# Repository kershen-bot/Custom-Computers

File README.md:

# Custom-Computer

 This is a fully custom laptop that is built around a LattePanda Mu, which is a computer module that is credit card-sized. This project took around two to three and a half months. This project is inspired by Ben Makes Everything and Bryan. The specific video by Ben Makes Everything that I used is "https://www.youtube.com/watch?v=o00P7wHbd2c," and the video by Bryan that I used is "https://www.youtube.com/watch?v=fks3PBodyiE." Bryan's website is "https://www.byran.ee/" 

 Below is an image of the full shell of the custom laptop without the hinge mechanism and the internal components.

------------------------------------------------------------------------------------------------------------------------------------------

Configuration of the Lattepanda Mu,
------------------------------------------------------------------------------------------------------------------------------------------
  The exact size of the Lattepanda Mu is 69.6MM by 60MM, and the standard credit card is 85.6MM by 54MM it is very. The Lattepanda Mu has an  Intel X86 chip. It can be configured with an   N100  or an  N305 chip.  The ram that on the Lattepanda Mu is 16GB of LPDDR5 4800MT/s, and for storage, it can be equipped with an M.2 2230 NVME SSD or slash and a 64GB eMMC 5.1 Storage. And of course it has a wifi card, so you can have wifi. 

Configuration of the LattePanda Mu,
The configuration of the full device is shown below as an image.
------------------------------------------------------------------------------------------------------------------------------------------

The Keyboard,
------------------------------------------------------------------------------------------------------------------------------------------
  The keyboard is a split Ortholinear keyboard because Ortholinear keyboards are easier and more natural to use. The keyboard is a fork of  Ben Makes Everything's first keyboard from his video "Building a LattePanda Mu Cyberdeck." The link to his video is https://www.youtube.com/watch?v=o00P7wHbd2c, and the time that the Ortholinear keyboard is mentioned is between the times 5:10 and 8:45. I learned how to make a  keyboard from "https://www.youtube.com/@joe_scotto"

The Trackpad on the computer,
------------------------------------------------------------------------------------------------------------------------------------------
 The trackpad is made by the company Azoteq, and the exact trackpad that I use is the PXM0091. Azoteq says itself "The IQS9150 is a generic and configurable trackpad device aimed to be suitable for numerous design variations and requirements. The PXM0091 utilizes the IQS9150 to provide high-performance multitouch (linearity, accuracy, low-noise) trackpad outputs, switch input, and an on-chip gesture recognition engine. The website that I got it from was "https://seltech-intl.com/datasheets/pxm0091.pdf." 

The ports on the Laptop,
------------------------------------------------------------------------------------------------------------------------------------------
  The laptop has four USB ports in the style of a Raspberry Pi. The HDMI port is on the back, like some gaming laptops, such as the HP OMEN MAX 16. There are a few internal USB ports, but not use the traditional ribbon connectors and cables; instead, it is using a JST connector, and there is an internal amp on the mainboard, but the BIOS and  LattePanda Mu software do not support I2S.  LattePanda said, "They will support I2S in the near future." So I decided to use a USB to audio using a rapberry pi pico to I2S, then I2S to a  USB audio converter, then to the speaker. 

The Power System
------------------------------------------------------------------------------------------------------------------------------------------
  The power button is on the main board, and it is internal, but the reason why is that when testing it, you don't need to go to the side of the laptop. But how to turn on the computer, you may ask. There is a keyboard switch on the side of the computer that is wired to the internal power button. All so there is a switch that connects directly to the battery and skips the main board and all of the software, so in an emergency, you canan switch it, and all power is shut off immediately  The battery is a 18650 4S5P battery pacl connected to an trusted AliExpress BMS, which is the  "140W 2S 3S 4S 5S 6S Lithium Battery Charging Board Bidirectional Fast Charging Li-ion Lifepo4 BMS Charger Type-C IP2366 PD3.1". Which is then connected to a 100A ANL fuse. Then it goes to a screw terminal and connects to the main board with another screw terminal, which takes the 9-12 volts from the battery. 

Battery Life of the laptop
------------------------------------------------------------------------------------------------------------------------------------------
  Battery life is a key thing when using a laptop. When you have a small battery, you have a little time on the battery, and when you have a big battery, your batter last a long time.
Number for Battery Life of the laptop
1. The battery life is about 7 hours in high-performance mode.
2. 10 hours on balanced mode.
3. On battery saver mode. It lasts about 15 hours.
  These numbers are done by math but not tested in the real world. The amount of watt-hours in the battery is 120-176 watt-hours. The legal limit for laptops that can go on planes is 99.99 watt-hours, and for battery banks it is 120-176. So if you decide to make this laptop, you can't bring it on a plane, so you have to send it to the location.

Sources & bibliography
------------------------------------------------------------------------------------------------------------------------------------------
Here are some sources I used during this project.
Keybourd
1. https://lowprokb.ca/products/kailh-choc-low-profile-switches
2. https://www.youtube.com/watch?v=bBon6WwkdJE
3. https://www.youtube.com/watch?v=8WXpGTIbxlQ
4. https://www.youtube.com/@joe_scotto
5. https://github.com/qmk/qmk_firmware
6. https://qmk.fm/
Trackpad
1. https://www.mouser.com/datasheet/2/42/Azoteq_PXM0057_20220503-2943524.pdf
2. https://www.azoteq.com/product/pxm0091/
3. https://www.mouser.ca/ProductDetail/Azoteq/IQS9150EV02-S?qs=wT7LY0lnAe1UXNco1GldIA%3D%3D
4. https://www.mouser.ca/datasheet/3/931/1/iqs9150ev02_user_guide.pdf
Battery
1. https://www.lipolbattery.com/lithium%20polymer%20battery.html
2. https://www.amazon.ca/s?k=thin+li+po+battery&rh=n%3A667823011%2Cp_n_feature_five_browse-bin%3A23876309011&dc&ds=v1%3A1%2FyLAj4am5oxl1W0bAFB4SyuocLMjKd7XB4K8g09IpI&crid=1DQOK09KIS3O2&qid=1745368113&rnid=23876298011&sprefix=thin+li+po+battery+%2Caps%2C190&ref=sr_nr_p_n_feature_five_browse-bin_1

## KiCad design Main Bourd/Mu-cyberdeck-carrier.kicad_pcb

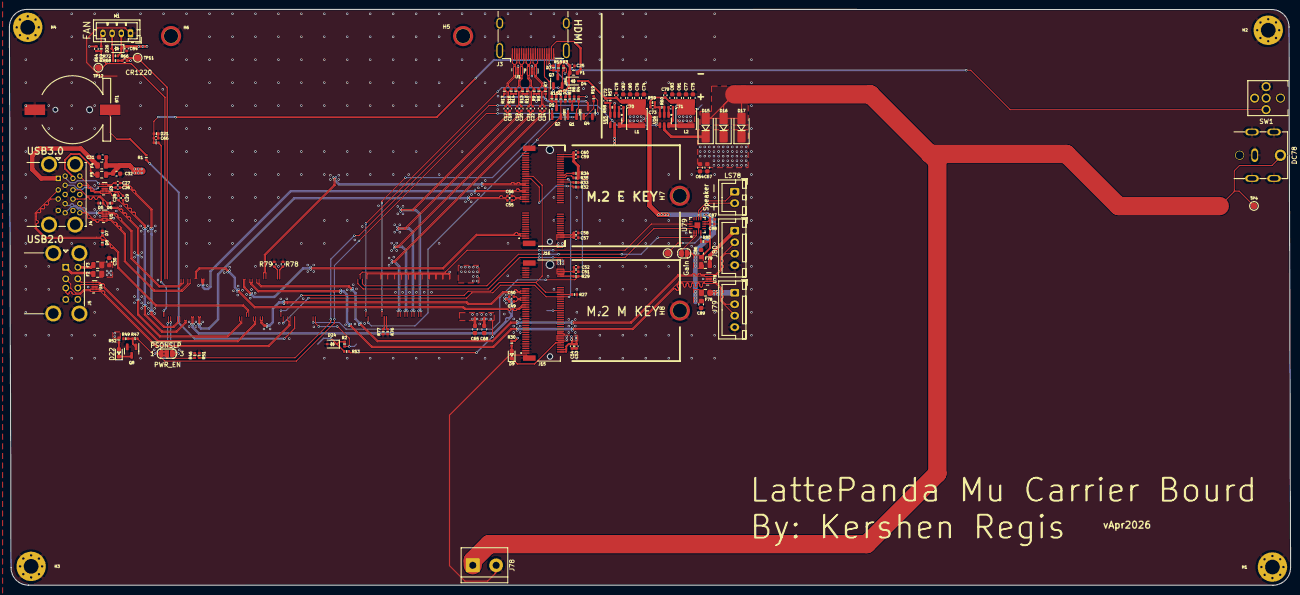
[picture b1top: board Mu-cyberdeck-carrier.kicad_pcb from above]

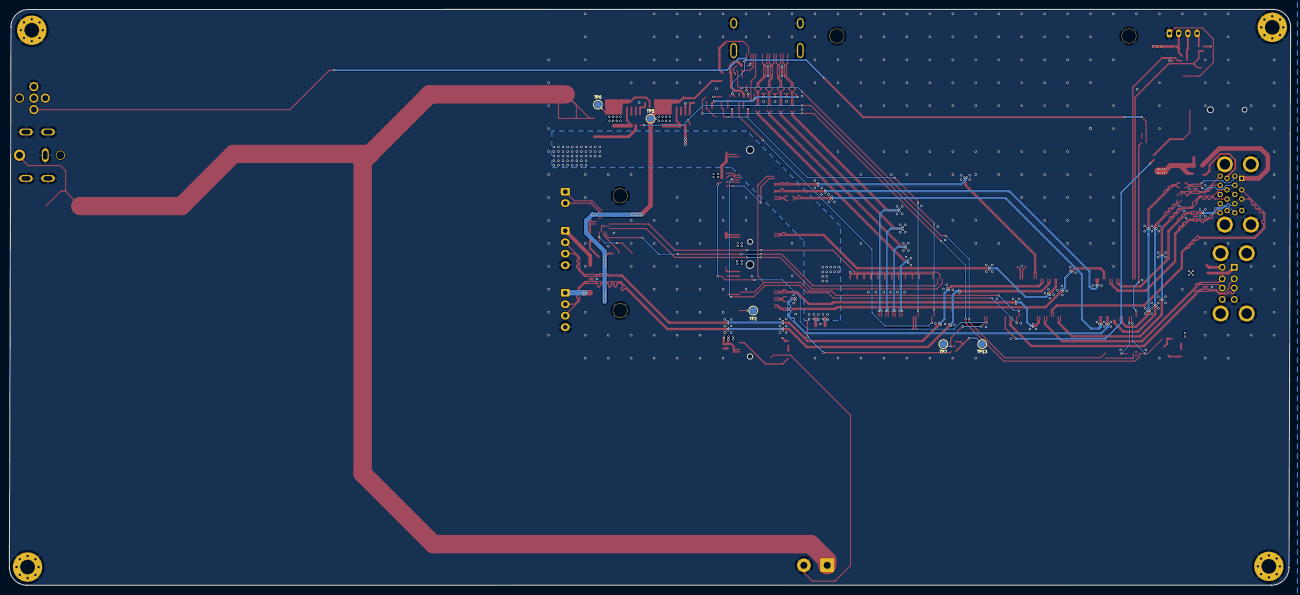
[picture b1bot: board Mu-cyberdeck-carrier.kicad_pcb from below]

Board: 4 copper layers, 279.0 x 125.4 mm, 169 parts (5 on the bottom side), 90 nets.

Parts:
BT1: Battery_Cell; Battery_Holder_CR1220_S8411-45R
C17, C18, C19, C20, C21, C22, C23, C24, C25, C26, C27, C28, C29, C52, C54, C58, C60, C70, C71, C78, C79, C84: 100nF/50V; C_0402_1005Metric
C30, C31, C32, C64, C65, C67, C68, C74, C75, C76, C77, C80, C81, C82, C83, C86, C89: 22uF/10V; C_0603_1608Metric
C49, C50, C55, C56: 220nF/50V; C_0402_1005Metric
C51, C53, C57, C59: 10uF/10V; C_0402_1005Metric
C66: 1uF/16V; C_0402_1005Metric
C72, C73: 12pF/50V; C_0402_1005Metric
C87: 10uF; C_0402_1005Metric
C88: 100nF; C_0402_1005Metric
D1, D2, D3, D5, D6, D7, D8, D21: ESD5V0B03; D_0402_1005Metric
D4, D26: 1N5819WS; D_SOD-323
D9, D22: LED_G; LED_0603_1608Metric
D15, D16, D17: SS54; D_SMA
D24: 3V3 Izt=5mA; D_SOD-323
DC78: DC-042C-W-2.0; DC-IN-TH_DC-042C-W-2.0
F1: 6V/50mA; R_0603_1608Metric
F2, F3, F78, F79: 6V/1A; Fuse_0805_2012Metric
F4: 6V/2A; R_0805_2012Metric
F5: 6V/2A; Fuse_0805_2012Metric
Gain: SolderJumper_2_Open; SolderJumper-2_P1.3mm_Open_RoundedPad1.0x1.5mm
H1, H2, H3, H4: MountingHole_Pad; MountingHole_3.2mm_M3_Pad_Via
H5, H6: MountingHole_Pad; MountingHole_3mm_M2_Pad_TopOnly
H7, H8: MountingHole_M2.0; MountingHole_3mm_M2_Pad_TopOnly
J3: HDMI_A; HDMI_A_Molex_208658-1001_Horizontal
J4: USB3_A_Stacked; USB3_A_Molex_48406-0001_Horizontal_Stacked
J5: USB_A_Stacked; USB_A_CUI_UJ2-ADH-TH_Horizontal_Stacked
J15: Bus_M.2_Socket_M; PCIe_M.2_Connectors_P=0.5mm_H=4.2mm_KeyM
J16: Bus_M.2_Socket_E; PCIe_M.2_Connectors_P=0.5mm_H=4.2mm_KeyE
J78: Screw_Terminal_01x02; TerminalBlock_bornier-2_P5.08mm
J79, J80: Conn_01x04_Socket; JST_XH_B4B-XH-A_1x04_P2.50mm_Vertical
JP79: SolderJumper_3_Open; SolderJumper-3_P1.3mm_Bridged2Bar12_RoundedPad1.0x1.5mm_Num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
L1, L2: 2.2uH/4.3A; L_Sunlord_SWPA4020S
LS78: Speaker; JST_XH_B2B-XH-A_1x02_P2.50mm_Vertical
M1: Fan_4pin; JST_PH_B4B-PH-K_1x04_P2.00mm_Vertical
Q1, Q8: 2N7002; SOT-23
Q2, Q3, Q4: 2SK3018; SOT-23
R1, R11, R47: 1K/1%; R_0402_1005Metric
R2, R34, R35, R49, R58, R78, R79: 10K/1%; R_0402_1005Metric
R3, R5, R15, R18, R19, R30, R52, R53: 2.2K/1%; R_0402_1005Metric
R4: 1M/1%; R_0402_1005Metric
R6, R59, R66, R68: 21.5K/1%; R_0402_1005Metric
R7, R8, R9, R10, R13, R14, R16, R17: 470R/1%; R_0402_1005Metric
R27, R29, R32, R33: 0R/1%; R_0402_1005Metric
R46, R48, R69: 100R/1%; R_0402_1005Metric
R51, R76, R77: 100K/1%; R_0402_1005Metric
R57: 75K/1%; R_0402_1005Metric
R60, R64, R72: 4.7K/1%; R_0402_1005Metric
R80: 1M; R_0402_1005Metric
SD_Mode: TestPoint; TestPoint_Pad_D1.5mm
SW1: SW_Push; SW-TH_TM-007-D1-A-03
TP2, TP4, TP5, TP6, TP7, TP11, TP12, TP13: TestPoint; TestPoint_Pad_D1.5mm
U1, U2: TPAZ1023-04F; Diodes_UDFN-10_1.0x2.5mm_P0.5mm
U3, U4, U5, U78: ULC0524P; Diodes_UDFN-10_1.0x2.5mm_P0.5mm
U15, U16: SY8253ADC; TSOT-23-6
U79: MAX98357AETE+T; 21-0136I_T1633-4_MXM

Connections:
5V_HDMI_VCC: C25.1, D4.1 (K), F1.1, R15.1, R18.1
+3V3: C51.2, C52.2, C53.2, C54.2, C57.2, C58.2, C59.2, C60.2, C73.1, C75.2, C77.2, C79.1, C81.2, C83.2, J15.2 (3.3V), J15.4 (3.3V), J15.12 (3.3V), J15.14 (3.3V), J15.16 (3.3V), J15.18 (3.3V), J15.70 (3.3V), J15.72 (3.3V), J15.74 (3.3V), J16.2 (3.3V), J16.4 (3.3V), J16.72 (3.3V), J16.74 (3.3V), L2.2, Q1.1 (G), Q2.1 (G), Q3.1 (G), R3.1, R4.1, R5.1, R30.2, R34.2, R35.1, R52.2, R59.2, R64.1, TP6.1
+5V: C30.2, C31.2, C32.2, C72.1, C74.2, C76.2, C78.1, C80.2, C82.2, C84.1, C86.2, C87.1, C88.1, C89.2, D4.2 (A), D26.1 (K), F2.1, F3.1, F4.1, F5.1, F78.1, F79.1, Gain.1 (A), L1.2, M1.2 (+), R57.2, R72.1, R80.1, TP5.1, U79.7 (VDD), U79.8 (VDD)
+12V: D15.2 (A), D16.2 (A), D17.2 (A), DC78.4, J78.1, TP4.1
/Fan_Temp/FAN_1_PWM: R64.2, R69.1, TP12.1
/Fan_Temp/FAN_1_TAC: R66.1, R68.2, TP11.1
/HDMI/DDC_SCL: D1.2 (A2), J3.15 (SCL), Q2.3 (D), R15.2
/HDMI/DDC_SDA: D3.2 (A2), J3.16 (SDA), Q3.3 (D), R18.2
/HDMI/DDI_B_DDC_SCL: Q2.2 (S), R5.2
/HDMI/DDI_B_DDC_SDA: Q3.2 (S), R3.2
/HDMI/DDI_B_HPD: Q1.2 (S), R4.2
/HDMI/HPD: D2.2 (A2), J3.19 (HPD), R11.2
/HDMI/TMDS_CK+: C23.2, J3.10 (CK+), R8.1, U2.4, U2.7 (NC)
/HDMI/TMDS_CK-: C24.2, J3.12 (CK-), R7.1, U2.5, U2.6 (NC)
/HDMI/TMDS_D0+: C21.2, J3.7 (D0+), R10.1, U2.1, U2.10 (NC)
/HDMI/TMDS_D0-: C22.2, J3.9 (D0-), R9.1, U2.2, U2.9 (NC)
/HDMI/TMDS_D1+: C19.2, J3.4 (D1+), R14.1, U1.4, U1.7 (NC)
/HDMI/TMDS_D1-: C20.2, J3.6 (D1-), R13.1, U1.5, U1.6 (NC)
/HDMI/TMDS_D2+: C17.2, J3.1 (D2+), R17.1, U1.1, U1.10 (NC)
/HDMI/TMDS_D2-: C18.2, J3.3 (D2-), R16.1, U1.2, U1.9 (NC)
/LattePanda Module/SUSCLK_WIFI: R29.2, R33.2
/M.2 E&M Key/CON_PCIE_TX_0+: C55.2, J16.35 (PETp0)
/M.2 E&M Key/CON_PCIE_TX_0-: C56.2, J16.37 (PETn0)
/M.2 E&M Key/CON_PCIE_TX_1+: C49.2, J15.49 (PETp0/SATA-A+)
/M.2 E&M Key/CON_PCIE_TX_1-: C50.2, J15.47 (PETn0/SATA-A-)
/M.2 E&M Key/~CLKREQE: J16.53 (~CLKREQ0), R32.1
/M.2 E&M Key/~CLKREQM: J15.52 (~CLKREQ), R27.1
/PSU/PWR_EN: R46.2, R51.2, U15.4 (EN), U16.4 (EN)
/USB2.0&USB3.0/CON_USB1_D_N: J5.2 (D1-), U4.2, U4.9 (NC)
/USB2.0&USB3.0/CON_USB1_D_P: J5.3 (D1+), U4.1, U4.10 (NC)
/USB2.0&USB3.0/CON_USB2_D_N: J5.6 (D2-), U4.5, U4.6 (NC)
/USB2.0&USB3.0/CON_USB2_D_P: J5.7 (D2+), U4.4, U4.7 (NC)
/USB2.0&USB3.0/CON_USB3_D_N: D8.2 (A2), J4.2 (D1-)
/USB2.0&USB3.0/CON_USB3_D_P: D7.2 (A2), J4.3 (D1+)
/USB2.0&USB3.0/CON_USB3_SSRX_N: J4.5 (SSRX1-), U5.4, U5.7 (NC)
/USB2.0&USB3.0/CON_USB3_SSRX_P: J4.6 (SSRX1+), U5.5, U5.6 (NC)
/USB2.0&USB3.0/CON_USB3_SSTX_N: C26.2, J4.8 (SSTX1-), U3.4, U3.7 (NC)
/USB2.0&USB3.0/CON_USB3_SSTX_P: C27.2, J4.9 (SSTX1+), U3.5, U3.6 (NC)
/USB2.0&USB3.0/CON_USB4_D_N: D6.2 (A2), J4.11 (D2-)
/USB2.0&USB3.0/CON_USB4_D_P: D5.2 (A2), J4.12 (D2+)
/USB2.0&USB3.0/CON_USB4_SSRX_N: J4.14 (SSRX2-), U5.1, U5.10 (NC)
/USB2.0&USB3.0/CON_USB4_SSRX_P: J4.15 (SSRX2+), U5.2, U5.9 (NC)
/USB2.0&USB3.0/CON_USB4_SSTX_N: C28.2, J4.17 (SSTX2-), U3.1, U3.10 (NC)
/USB2.0&USB3.0/CON_USB4_SSTX_P: C29.2, J4.18 (SSTX2+), U3.2, U3.9 (NC)
/~PLT_RST: J15.50 (~PERST), J16.52 (~PERST0)
/~PWR_LED/~PSON: JP79.1 (A), R19.1, R47.1
/~WAKE: J15.54 (~PEWAKE), J16.55 (~PEWAKE0)
GND: BT1.2 (-), C25.2, C30.1, C31.1, C32.1, C51.1, C52.1, C53.1, C54.1, C57.1, C58.1, C59.1, C60.1, C64.1, C65.1, C66.2, C67.1, C68.1, C74.1, C75.1, C76.1, C77.1, C78.2, C79.2, C80.1, C81.1, C82.1, C83.1, C84.2, C86.1, C87.2, C88.2, C89.1, D1.1 (A1), D2.1 (A1), D3.1 (A1), D5.1 (A1), D6.1 (A1), D7.1 (A1), D8.1 (A1), D21.1 (A1), D24.2 (A), DC78.2, DC78.3, H1.1, H2.1, H3.1, H4.1, H5.1, H6.1, H7.1, H8.1, J3.2 (D2S), J3.5 (D1S), J3.8 (D0S), J3.11 (CKS), J3.17 (GND), J3.SH, J4.4 (GND1), J4.7 (DRAIN1), J4.13 (GND2), J4.16 (DRAIN2), J4.19 (SHIELD), J5.4 (GND1), J5.8 (GND2), J5.9 (Shield), J15.1 (GND), J15.3 (GND), J15.9 (GND), J15.15 (GND), J15.21 (GND), J15.27 (GND), J15.33 (GND), J15.39 (GND), J15.45 (GND), J15.51 (GND), J15.57 (GND), J15.71 (GND), J15.73 (GND), J15.75 (GND), J15.MP1, J15.MP2, J16.1 (GND), J16.7 (GND), J16.18 (GND), J16.33 (GND), J16.39 (GND), J16.45 (GND), J16.51 (GND), J16.57 (GND), J16.63 (GND), J16.69 (GND), J16.75 (GND), J16.MP1, J16.MP2, J78.2, J79.4, J80.4, M1.1 (-), Q4.2 (S), Q8.2 (S), R6.2, R27.2, R32.2, R49.1, R51.1, R58.1, R60.1, R66.2, R76.2, R77.2, R78.2, R79.2, SW1.2, U1.3 (VSS), U1.8 (VSS), U2.3 (VSS), U2.8 (VSS), U3.3 (VSS), U3.8 (VSS), U4.3 (VSS), U4.8 (VSS), U5.3 (VSS), U5.8 (VSS), U15.2 (GND), U16.2 (GND), U78.3 (VSS), U78.8 (VSS), U79.3 (GND), U79.11 (GND), U79.15 (GND), U79.17 (EPAD)
unnamed: R2.1, TP7.1
unnamed: BT1.1 (+), R1.2
unnamed: D9.2 (A), R30.1
unnamed: D9.1 (K), J15.10 (DAS/~DSS/~LED1)
unnamed: D22.2 (A), R52.1
unnamed: D22.1 (K), Q8.3 (D)
unnamed: D26.2 (A), M1.3 (Tacho), R68.1, R72.2
unnamed: F1.2, J3.18 (+5V)
unnamed: F4.2, J4.1 (VBUS1)
unnamed: F5.2, J4.10 (VBUS2)
unnamed: F2.2, J5.1 (VBUS1)
unnamed: F3.2, J5.5 (VBUS2)
unnamed: J15.38 (DEVSLP), TP2.1
unnamed: J15.68 (SUSCLK), R29.1
unnamed: J16.50 (SUSCLK), R33.1
unnamed: J16.56 (~W_DISABLE1), R34.1
unnamed: J16.54 (~W_DISABLE2), R35.2
unnamed: F78.2, J79.1
unnamed: F79.2, J80.1
unnamed: Gain.2 (B), U79.2 (GAIN_SLOT)
unnamed: JP79.2 (C), R46.1
unnamed: M1.4 (PWM), R69.2
unnamed: Q1.3 (D), R6.1, R11.1
unnamed: Q4.3 (D), R7.2, R8.2, R9.2, R10.2, R13.2, R14.2, R16.2, R17.2
unnamed: Q4.1 (G), R19.2
unnamed: Q8.1 (G), R47.2, R49.2
unnamed: C70.2, U15.1 (BOOST)
unnamed: C72.2, R57.1, R58.2, U15.3 (FB)
unnamed: C70.1, L1.1, U15.6 (SW)
unnamed: C71.2, U16.1 (BOOST)
unnamed: C73.2, R59.1, R60.2, U16.3 (FB)
unnamed: C71.1, L2.1, U16.6 (SW)
unnamed: R80.2, SD_Mode.1, U79.4 (*SD_MODE)
unnamed: LS78.1, U79.10 (OUTN)
unnamed: LS78.2, U79.9 (OUTP)
PWR: C66.1, D21.2 (A2), R48.1, SW1.1
USB_2_FP1+: J79.3, U78.1, U78.10 (NC)
USB_2_FP1-: J79.2, U78.2, U78.9 (NC)
USB_2_FP2+: J80.3, U78.4, U78.7 (NC)
USB_2_FP2-: J80.2, U78.5, U78.6 (NC)
VDC: C64.2, C65.2, C67.2, C68.2, D15.1 (K), D16.1 (K), D17.1 (K), R53.1, U15.5 (VIN), U16.5 (VIN)
VPullup: D24.1 (K), R2.2, R53.2, TP13.1

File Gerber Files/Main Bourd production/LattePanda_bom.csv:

Designator,Footprint,Quantity,Value,LCSC Part #
BT1,Battery_Holder_CR1220_S8411-45R,1,Battery_Cell,C964723
"C17, C18, C19, C20, C21, C22, C23, C24, C25, C26, C27, C28, C29, C52, C54, C58, C60, C70, C71, C78, C79, C84",0402,22,100nF/50V,
"C30, C31, C32, C64, C65, C67, C68, C74, C75, C76, C77, C80, C81, C82, C83, C86, C89",0603,17,22uF/10V,
"C49, C50, C55, C56",0402,4,220nF/50V,
"C51, C53, C57, C59",0402,4,10uF/10V,
C66,0402,1,1uF/16V,
C87,0402,1,10uF,
C88,0402,1,100nF,
"D1, D2, D21, D3, D5, D6, D7, D8",0402,8,ESD5V0B03,C521894
"D15, D16, D17",D_SMA,3,SS54,C5200096
"D22, D9",0603,2,LED_G,
D24,D_SOD-323,1,3V3 Izt=5mA,SOD-323
"D26, D4",D_SOD-323,2,1N5819WS,C191023
DC78,DC-IN-TH_DC-042C-W-2.0,1,DC-042C-W-2.0,C381108
F1,0603,1,6V/50mA,C7472508
"F2, F3, F78, F79",0805,4,6V/1A,C883108
F4,0805,1,6V/2A,C883112
F5,0805,1,6V/2A,C883108
"H5, H6",MountingHole_3mm_M2_Pad_TopOnly,2,MountingHole_Pad, C5301799
"H7, H8",MountingHole_3mm_M2_Pad_TopOnly,2,MountingHole_M2.0,C5301801
J15,PCIe_M.2_Connectors_P=0.5mm_H=4.2mm_KeyM,1,Bus_M.2_Socket_M,C7498140
J16,PCIe_M.2_Connectors_P=0.5mm_H=4.2mm_KeyE,1,Bus_M.2_Socket_E,C7498141
J3,HDMI_A_Molex_208658-1001_Horizontal,1,HDMI_A,C2906135
J4,USB3_A_Molex_48406-0001_Horizontal_Stacked,1,USB3_A_Stacked,C2895028
J5,USB_A_CUI_UJ2-ADH-TH_Horizontal_Stacked,1,USB_A_Stacked,C7527675
J78,TerminalBlock_bornier-2_P5.08mm,1,Screw_Terminal_01x02,C394556
"J79, J80",JST_XH_B4B-XH-A_1x04_P2.50mm_Vertical,2,Conn_01x04_Socket,C144395
"L1, L2",L_Sunlord_SWPA4020S,2,2.2uH/4.3A,C3222957
LS78,JST_XH_B2B-XH-A_1x02_P2.50mm_Vertical,1,Speaker,C495685
M1,JST_PH_B4B-PH-K_1x04_P2.00mm_Vertical,1,Fan_4pin,C131334
"Q1, Q8",SOT-23,2,2N7002,C727148
"Q2, Q3, Q4",SOT-23,3,2SK3018,C727148
"R1, R11, R47",0402,3,1K/1%,
"R10, R13, R14, R16, R17, R7, R8, R9",0402,8,470R/1%,
"R15, R18, R19, R3, R30, R5, R52, R53",0402,8,2.2K/1%,
"R2, R34, R35, R49, R58, R78, R79",0402,7,10K/1%,
"R27, R29, R32, R33",0402,4,0R/1%,
R4,0402,1,1M/1%,
"R46, R48, R69",0402,3,100R/1%,
"R51, R76, R77",0402,3,100K/1%,
R57,0402,1,75K/1%,
"R59, R6, R68",0402,3,21.5K/1%,
"R60, R72",0402,2,4.7K/1%,
R80,0402,1,1M,
SW1,SW-TH_TM-007-D1-A-03,1,SW_Push,C5184999
"TP2, TP4",TestPoint_Pad_D1.5mm,2,TestPoint,
"U1, U2",Diodes_UDFN-10_1.0x2.5mm_P0.5mm,2,TPAZ1023-04F,C1980462
"U15, U16",TSOT-23-6,2,SY8253ADC,C93736
"U3, U4, U5, U78",Diodes_UDFN-10_1.0x2.5mm_P0.5mm,4,ULC0524P,C1980462
U79,21-0136I_T1633-4_MXM,1,MAX98357AETE+T,C910544

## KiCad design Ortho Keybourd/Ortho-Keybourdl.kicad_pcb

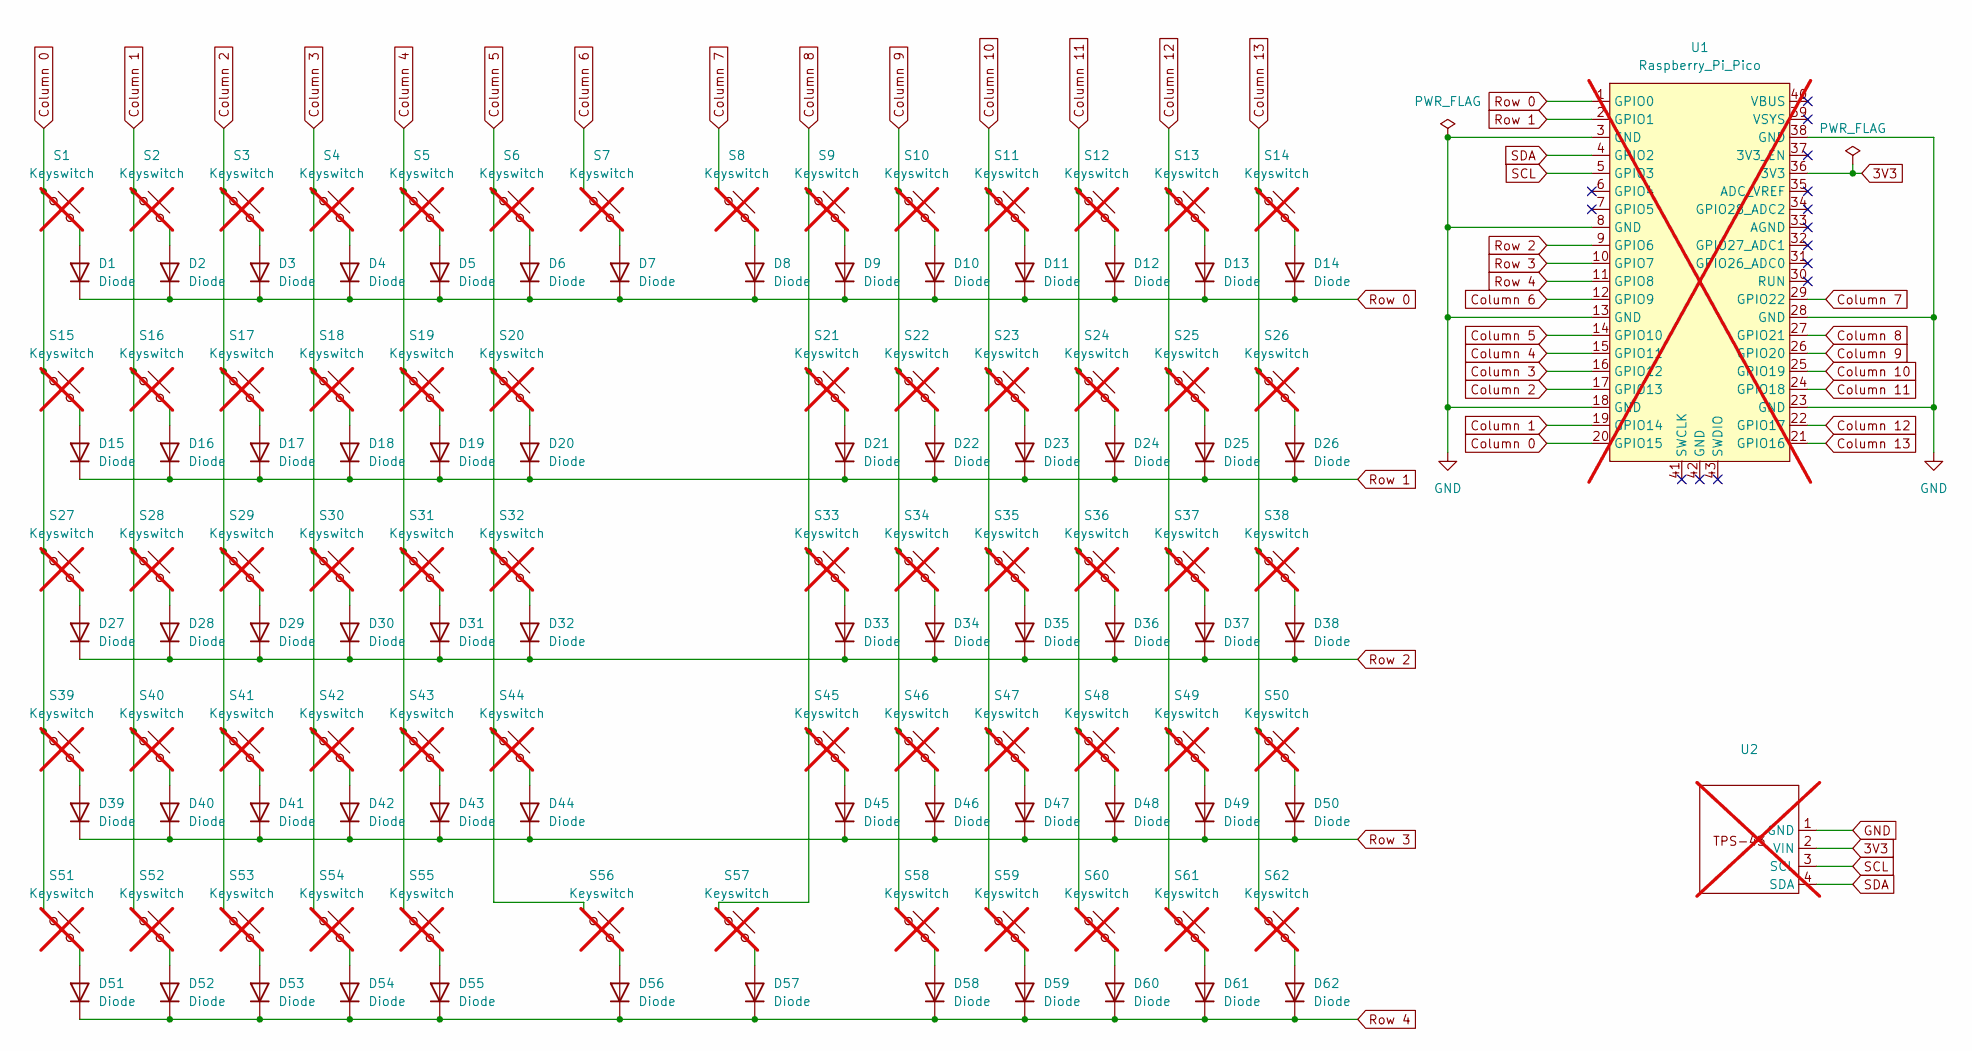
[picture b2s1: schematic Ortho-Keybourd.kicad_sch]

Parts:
D1, D2, D3, D4, D5, D6, D7, D8, D9, D10, D11, D12, D13, D14, D15, D16, D17, D18, D19, D20, D21, D22, D23, D24, D25, D26, D27, D28, D29, D30, D31, D32, D33, D34, D35, D36, D37, D38, D39, D40, D41, D42, D43, D44, D45, D46, D47, D48, D49, D50, D51, D52, D53, D54, D55, D56, D57, D58, D59, D60, D61, D62: Diode; Diode_SOD-123; MPN 1N4148W-7-F
S1, S2, S3, S4, S5, S6, S7, S8, S9, S10, S11, S12, S13, S14, S15, S16, S17, S18, S19, S20, S21, S22, S23, S24, S25, S26, S27, S28, S29, S30, S31, S32, S33, S34, S35, S36, S37, S38, S39, S40, S41, S42, S43, S44, S45, S46, S47, S48, S49, S50, S51, S52, S53, S54, S56, S57, S59, S60, S61, S62: Keyswitch; Choc_V1; not fitted
S55, S58: Keyswitch; Choc_V1_2.00u; not fitted
U1: Raspberry_Pi_Pico; not fitted
U2: PinHeader_1x04_P2.54mm_Vertical; not fitted

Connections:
3V3: U1.36 (3V3), U2.2 (VIN)
Column 0: S1.1, S15.1, S27.1, S39.1, S51.1, U1.20 (GPIO15)
Column 1: S2.1, S16.1, S28.1, S40.1, S52.1, U1.19 (GPIO14)
Column 2: S3.1, S17.1, S29.1, S41.1, S53.1, U1.17 (GPIO13)
Column 3: S4.1, S18.1, S30.1, S42.1, S54.1, U1.16 (GPIO12)
Column 4: S5.1, S19.1, S31.1, S43.1, S55.1, U1.15 (GPIO11)
Column 5: S6.1, S20.1, S32.1, S44.1, S56.1, U1.14 (GPIO10)
Column 6: S7.1, U1.12 (GPIO9)
Column 7: S8.1, U1.29 (GPIO22)
Column 8: S9.1, S21.1, S33.1, S45.1, S57.1, U1.27 (GPIO21)
Column 9: S10.1, S22.1, S34.1, S46.1, S58.1, U1.26 (GPIO20)
Column 10: S11.1, S23.1, S35.1, S47.1, S59.1, U1.25 (GPIO19)
Column 11: S12.1, S24.1, S36.1, S48.1, S60.1, U1.24 (GPIO18)
Column 12: S13.1, S25.1, S37.1, S49.1, S61.1, U1.22 (GPIO17)
Column 13: S14.1, S26.1, S38.1, S50.1, S62.1, U1.21 (GPIO16)
GND: U1.3 (GND), U1.8 (GND), U1.13 (GND), U1.18 (GND), U1.23 (GND), U1.28 (GND), U1.38 (GND), U2.1 (GND)
unnamed: D1.2 (A), S1.2
unnamed: D2.2 (A), S2.2
unnamed: D3.2 (A), S3.2
unnamed: D4.2 (A), S4.2
unnamed: D5.2 (A), S5.2
unnamed: D6.2 (A), S6.2
unnamed: D7.2 (A), S7.2
unnamed: D8.2 (A), S8.2
unnamed: D9.2 (A), S9.2
unnamed: D10.2 (A), S10.2
unnamed: D11.2 (A), S11.2
unnamed: D12.2 (A), S12.2
unnamed: D13.2 (A), S13.2
unnamed: D14.2 (A), S14.2
unnamed: D15.2 (A), S15.2
unnamed: D16.2 (A), S16.2
unnamed: D17.2 (A), S17.2
unnamed: D18.2 (A), S18.2
unnamed: D19.2 (A), S19.2
unnamed: D20.2 (A), S20.2
unnamed: D21.2 (A), S21.2
unnamed: D22.2 (A), S22.2
unnamed: D23.2 (A), S23.2
unnamed: D24.2 (A), S24.2
unnamed: D25.2 (A), S25.2
unnamed: D26.2 (A), S26.2
unnamed: D27.2 (A), S27.2
unnamed: D28.2 (A), S28.2
unnamed: D29.2 (A), S29.2
unnamed: D30.2 (A), S30.2
unnamed: D31.2 (A), S31.2
unnamed: D32.2 (A), S32.2
unnamed: D33.2 (A), S33.2
unnamed: D34.2 (A), S34.2
unnamed: D35.2 (A), S35.2
unnamed: D36.2 (A), S36.2
unnamed: D37.2 (A), S37.2
unnamed: D38.2 (A), S38.2
unnamed: D39.2 (A), S39.2
unnamed: D40.2 (A), S40.2
unnamed: D41.2 (A), S41.2
unnamed: D42.2 (A), S42.2
unnamed: D43.2 (A), S43.2
unnamed: D44.2 (A), S44.2
unnamed: D45.2 (A), S45.2
unnamed: D46.2 (A), S46.2
unnamed: D47.2 (A), S47.2
unnamed: D48.2 (A), S48.2
unnamed: D49.2 (A), S49.2
unnamed: D50.2 (A), S50.2
unnamed: D51.2 (A), S51.2
unnamed: D52.2 (A), S52.2
unnamed: D53.2 (A), S53.2
unnamed: D54.2 (A), S54.2
unnamed: D55.2 (A), S55.2
unnamed: D56.2 (A), S56.2
unnamed: D57.2 (A), S57.2
unnamed: D58.2 (A), S58.2
unnamed: D59.2 (A), S59.2
unnamed: D60.2 (A), S60.2
unnamed: D61.2 (A), S61.2
unnamed: D62.2 (A), S62.2
Row 0: D1.1 (K), D2.1 (K), D3.1 (K), D4.1 (K), D5.1 (K), D6.1 (K), D7.1 (K), D8.1 (K), D9.1 (K), D10.1 (K), D11.1 (K), D12.1 (K), D13.1 (K), D14.1 (K), U1.1 (GPIO0)
Row 1: D15.1 (K), D16.1 (K), D17.1 (K), D18.1 (K), D19.1 (K), D20.1 (K), D21.1 (K), D22.1 (K), D23.1 (K), D24.1 (K), D25.1 (K), D26.1 (K), U1.2 (GPIO1)
Row 2: D27.1 (K), D28.1 (K), D29.1 (K), D30.1 (K), D31.1 (K), D32.1 (K), D33.1 (K), D34.1 (K), D35.1 (K), D36.1 (K), D37.1 (K), D38.1 (K), U1.9 (GPIO6)
Row 3: D39.1 (K), D40.1 (K), D41.1 (K), D42.1 (K), D43.1 (K), D44.1 (K), D45.1 (K), D46.1 (K), D47.1 (K), D48.1 (K), D49.1 (K), D50.1 (K), U1.10 (GPIO7)
Row 4: D51.1 (K), D52.1 (K), D53.1 (K), D54.1 (K), D55.1 (K), D56.1 (K), D57.1 (K), D58.1 (K), D59.1 (K), D60.1 (K), D61.1 (K), D62.1 (K), U1.11 (GPIO8)
SCL: U1.5 (GPIO3), U2.3 (SCL)
SDA: U1.4 (GPIO2), U2.4 (SDA)

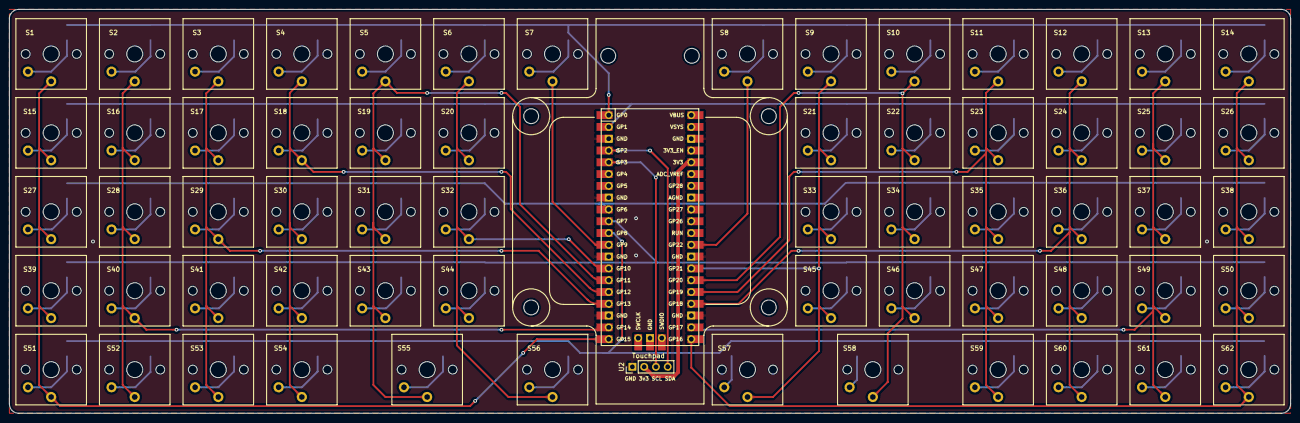
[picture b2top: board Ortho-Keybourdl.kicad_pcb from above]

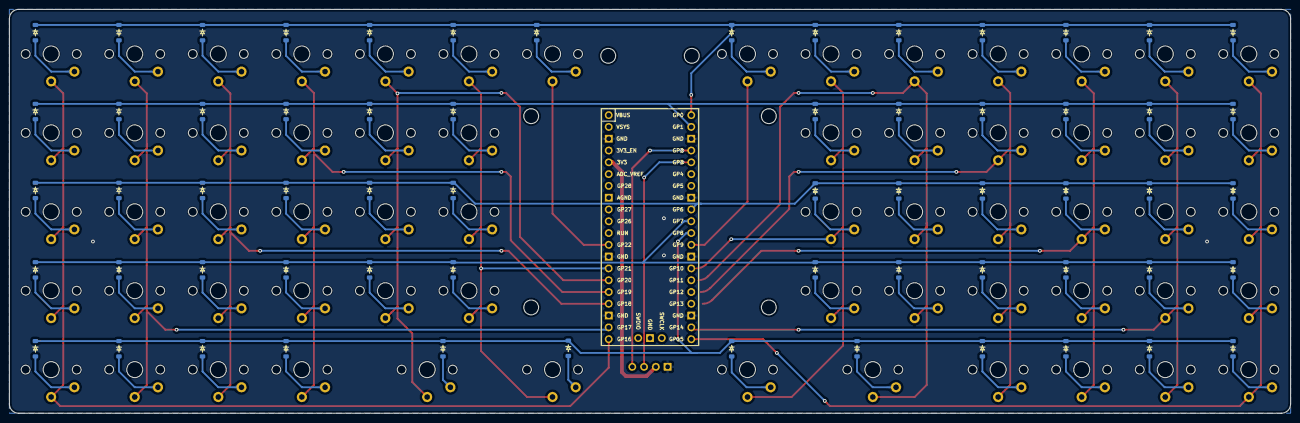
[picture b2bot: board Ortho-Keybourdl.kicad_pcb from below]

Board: 2 copper layers, 276.0 x 87.0 mm, 126 parts (62 on the bottom side), 85 nets.

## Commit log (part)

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2026-06-09 Remove .DS_Store files
2026-06-09 Add .DS_Store to .gitignore
2026-06-10 README.md
2026-06-25 Enhance README with project details and references
    Updated the README to include project inspirations and links to related videos. Added image descriptions and improved formatting for clarity.
2026-06-25 Enhance README with hardware details and specifications
    Updated the README.md to provide detailed information about the keyboard, trackpad, laptop ports, power system, and battery life.
2026-06-25 Fix typos and enhance readability in README.md
    Corrected typos and improved clarity in the README.
2026-06-25 Update keyboard description in README.md
    Added a reference to Joe Scotto's YouTube channel for keyboard making.
